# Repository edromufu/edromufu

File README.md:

### Hi there 👋

<!--
**edromufu/edromufu** is a ✨ _special_ ✨ repository because its `README.md` (this file) appears on your GitHub profile.

Here are some ideas to get you started:

- 🔭 I’m currently working on ...
- 🌱 I’m currently learning ...
- 👯 I’m looking to collaborate on ...
- 🤔 I’m looking for help with ...
- 💬 Ask me about ...
- 📫 How to reach me: ...
- 😄 Pronouns: ...
- ⚡ Fun fact: ...
-->

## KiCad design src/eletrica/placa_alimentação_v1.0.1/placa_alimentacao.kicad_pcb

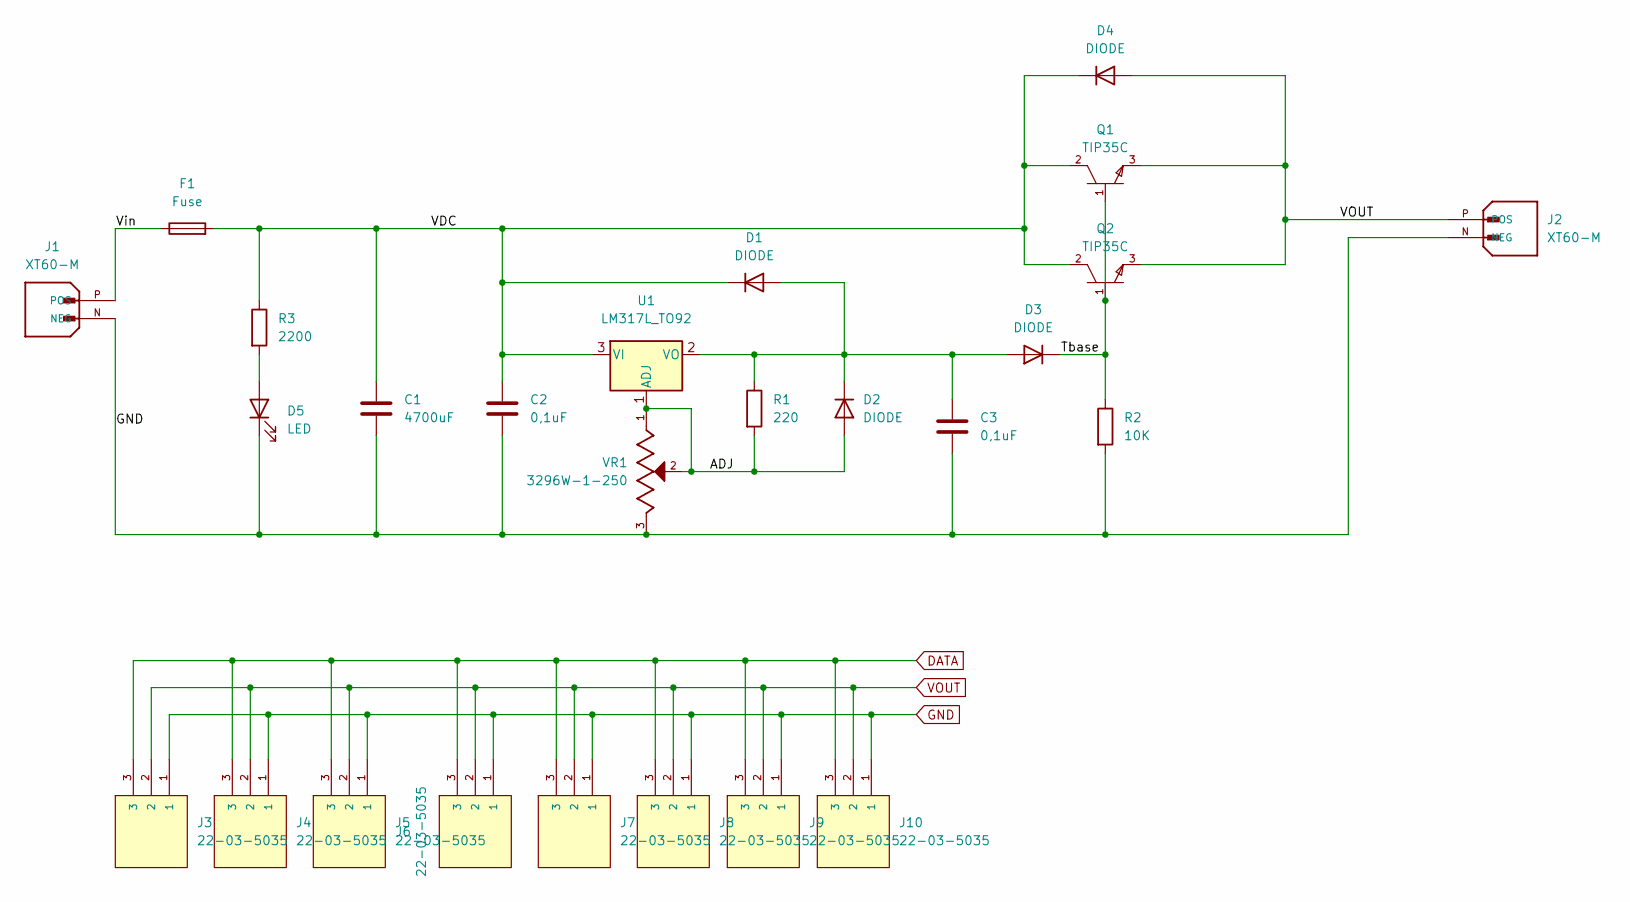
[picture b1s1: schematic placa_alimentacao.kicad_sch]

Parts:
C1: 4700uF; CP_Radial_D6.3mm_P2.50mm
C2, C3: 0,1uF; CP_Radial_D6.3mm_P2.50mm
D1, D2, D3, D4: DIODE; D_A-405_P12.70mm_Horizontal
D5: LED; LED_D3.0mm
F1: Fuse; Fuseholder_Cylinder-5x20mm_Schurter_0031_8201_Horizontal_Op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
J1, J2: XT60-M; AMASS_XT60-M; PARTREV V1.2
J3, J4, J5, J6, J7, J8, J9, J10: 22-03-5035; TTL_3pin; PARTREV B
Q1, Q2: TIP35C; TO-3PB-3_Vertical; voltage 100V; mouser part number 511-TIP35C; digikey description TRANS NPN 100V 25A TO-247
R1: 220; R_Axial_DIN0207_L6.3mm_D2.5mm_P7.62mm_Horizontal
R2: 10K; R_Axial_DIN0207_L6.3mm_D2.5mm_P7.62mm_Horizontal
R3: 2200; R_Axial_DIN0207_L6.3mm_D2.5mm_P7.62mm_Horizontal
U1: LM317L_TO92; TO-220-3_Vertical
VR1: 3296W-1-250; TRIM_3296W-1-250; PARTREV 05/16

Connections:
/ADJ: D2.1 (A), R1.2, U1.1 (ADJ), VR1.1, VR1.2
/Tbase: D3.2 (K), Q1.1 (BASE), Q2.1 (BASE), R2.1
/VDC: C1.1, C2.1, D1.2 (K), D4.2 (K), F1.2, Q1.2 (COLLECTOR), Q2.2 (COLLECTOR), R3.1, U1.3 (VI)
/Vin: F1.1, J1.P (POS)
DATA: J3.3, J4.3, J5.3, J6.3, J7.3, J8.3, J9.3, J10.3
GND: C1.2, C2.2, C3.2, D5.1 (K), J1.N (NEG), J2.N (NEG), J3.1, J4.1, J5.1, J6.1, J7.1, J8.1, J9.1, J10.1, R2.2, VR1.3
unnamed: C3.1, D1.1 (A), D2.2 (K), D3.1 (A), R1.1, U1.2 (VO)
unnamed: D5.2 (A), R3.2
VOUT: D4.1 (A), J2.P (POS), J3.2, J4.2, J5.2, J6.2, J7.2, J8.2, J9.2, J10.2, Q1.3 (EMITTER), Q2.3 (EMITTER)

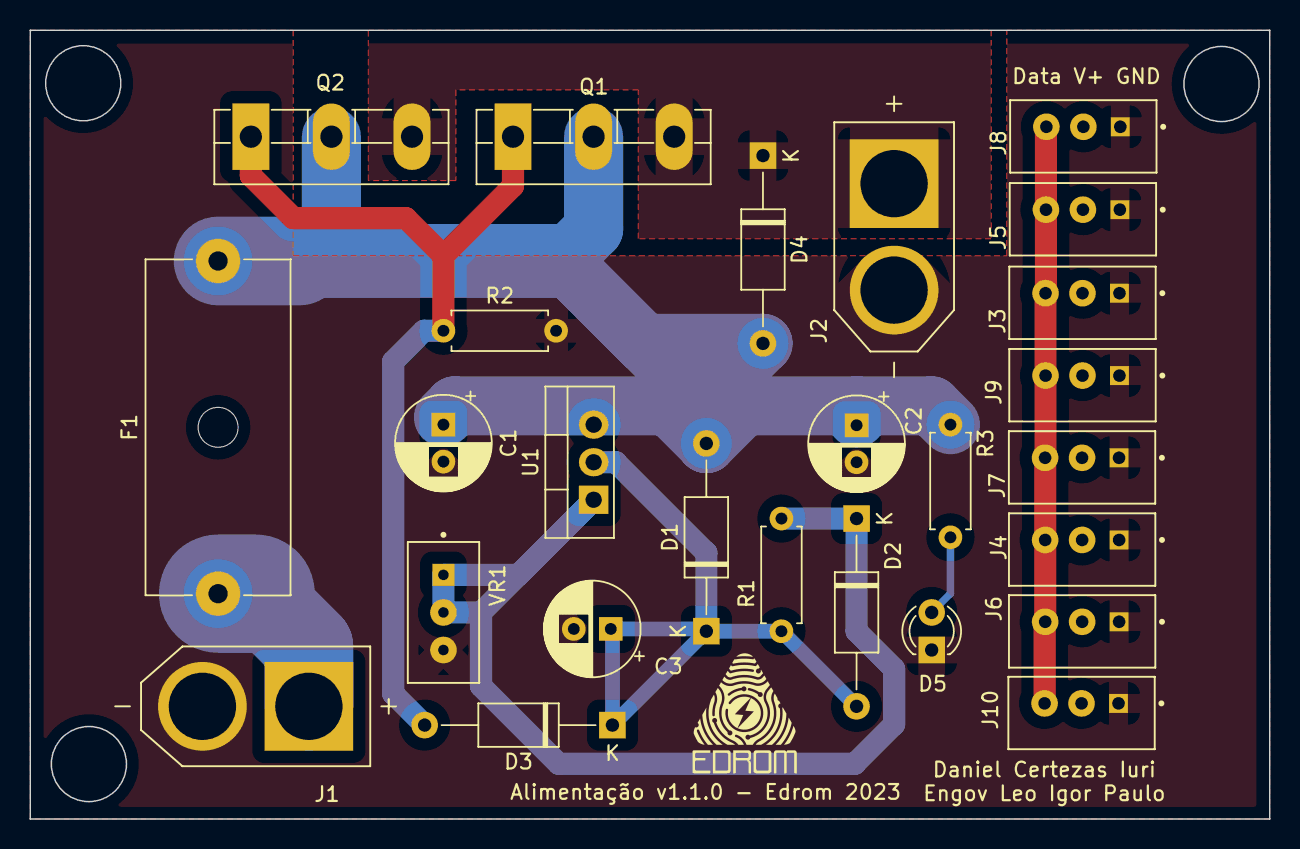
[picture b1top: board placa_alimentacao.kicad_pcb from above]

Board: 2 copper layers, 83.8 x 53.3 mm, 26 parts (0 on the bottom side), 9 nets.

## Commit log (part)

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2023-02-20 deploy: 3927a5f80aac86a664ac9377074125fa3db9a48a
2023-03-04 feat: updating SEO info
2023-03-09 Importação de .json no código de setup de robô, além de descrição da nova robô em .json.
2023-03-11 Alterações de QOL para o movimeto.
2023-03-11 Adição da cinemática direta funcional, com teste no setup_robot.py.
2023-03-15 Código da cinemática inversa.
2023-03-21 Adição dos motores invertidos, medidas da bioloid e alterações na mensagem de envio de posição aos motores.
2023-04-04 feat: adding placa da eletrica
2023-04-13 Page para VemPraUfu.
2023-04-27 Cinemática Inversa numérica funcional, remoção de pacotes iniciados antes da hora, alteração no .json da bioloid para mais complexo.
2023-04-28 Código da marcha funcional.
2023-05-04 Marcha funcional sem interpolação.
2023-05-05 Tentativa de interpolação.
2023-05-12 Solução burra de não conseguir chamar 2 marchas seguidas.
2023-05-12 deploy: 48f5c86a8db56971f9effe23fa8019512be7e65b
2023-05-12 deploy: de4b0d9f870d227b41426678e9c5c5853ad690d6
2023-05-12 deploy: 1f01412acf0f3dee689544b019c3a3a7313bde37
2023-05-12 deploy: cdb062678ca88378fecbfdf9b53d070c9acb654a
2023-05-12 deploy: 690ddbee62a3a7ab42929410748f4f81c1e6b5da
2023-05-12 deploy: 20d821d54e5ddaeca87752efcb6fc60e2abecab9
2023-05-12 deploy: 77052e3d364ca150665f6752ec5962a67bb86a9c
2023-05-13 deploy: a4d61b371b7a1144f42ccd0873185b7cab917576
2023-05-18 limitação dos joelhos para não quebrar
2023-05-26 Marcha sem interpolação funcional com joelho pro lado certo com problema de velocidade.
2023-06-01 Criação da classe padrão para juntas e início da classe padrão para robô.
2023-06-01 Fila no u2d2_comm
2023-07-03 Comunicação por grupos viável.
2023-07-03 Grupos funcionais e testado.
2023-07-10 Alterações no append não funcional da coree na comunicação com a u2d2.
2023-07-11 Removendo README da visão que gera conflito no merge com a dev.
2023-07-12 Interface no QtDesigner finalizada.
2023-07-12 Correção.
2023-07-17 Pacote da localizacao utilizando simulacao criado, parte da visao organizada com POO, commit para salvar alteracoes, mais testes serao feitos
2023-07-17 Funcionando para imagem, porem problemas na filtragem das interseccoes. Para testar no simulador, e necessario trocar o campo
2023-07-18 Teste para verificar tópico da estruturaaa
2023-07-18 Alterações restantes do QtDesigner.
2023-07-19 Botões já responsivos para o torque, posição atual sendo capturada e mostrada na tela.
2023-07-25 Pacote da localizacao real criado, com erro para matar o codigo. Intersecao filtrando corretamente, porem ajustes devem ser feitos. Ainda sem atualizacao das imagens quando utilizando ros (simulacao 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
2023-07-28 Resolvido bug de nao atualizar os frames, logica para evitar gargalos adicionada, mudanca na maneira de encontrar e verificar vizinhos, ainda nao foi possivel modificar o tamanho da imagem vinda da s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
2023-07-30 deploy: 2928f50e5e63d2a0b5530a4b819a7d1baaa1e23d
2023-07-30 deploy: 97fcbd00d635cccc3257c8d4f0158b8be7ad3756
2023-08-03 Commit do Igor
2023-08-04 Commit do Leo
2023-08-09 Pequena otimização na função de uncheck.
2023-08-10 Funcionalidade de salvar page implementada tanto para save quanto para saveAs.
2023-08-12 Cabeça funcional PARA A COMPETIÇÃO.
2023-08-12 Robô nova descrita em seu json, aparentemente a informação não esta sendo transmitida quando solicita-se publicação nos motores (u2d2 não pisca).
2023-08-18 Primeira tradução do código da simulação para o real
2023-08-22 BUG MX-106/MX-64
    Possível solução para não envio de posição para motores MX
2023-08-25 Codigo ligeiramente menos poluido
2023-08-29 Removendo movement antiga.
2023-08-30 Alterações do teste de marcha 29/08, software de pages funcional, conseguimos comandar posição pros motores, marcha não funcional.
2023-08-31 Visualizador pronto não integrado com a core.
2023-08-31 Visualizador funcional, pezinhos tortos na first_pose.
2023-09-02 Atualização do modelo da robô nova e de seu urdf.
2023-09-02 Separado corretamente e organizado o codigo, utilizando main temporaria para simulacao 2D
2023-09-05 deploy: 791abbdee91a0527ae1ee286bccd3fc24249245a
2023-09-05 deploy: 77e376e853058aa0c02f2170c94b71802796b567
2023-09-07 Page da natasha e atualização na core de QOL.
2023-09-10 IMU integrado com interpretações e testado, todas interpretações prontas sem teste.
2023-09-11 Implementações de QOL na leitura do código da u2d2, além de avisador de limites de motor. Não testado.
2023-09-11 Testado e funcional as implementações anteriores.
2023-09-12 Inicio da branch.
2023-09-16 Commitando para continuar de outro PC, nada funcional.
2023-09-17 Movimentação de procura e centralização da robô com NUC funcional, testar no NUC e implementar possível segundo código para PID.
2023-09-21 Tratamento de exceção no obtainMinMax.
2023-09-21 Calculador de poses do pé para caminhada pronto e não integrado (nem testado).
2023-09-24 Adicionando resize a visao para a melhora de FPS na jetson
2023-09-24 mudando os parametros de largura e altura da imagem da visao e mudando o nome do topico da visao
2023-09-25 First pose da aurea, teste do balanço funcional e interpolação para pose inicial.
2023-09-26 First pose da Natasha
2023-09-30 Removendo interpolação no geral.
2023-09-30 Pages da goleira funcional finalizando as defesas de costas,não há pages de se levantar.
2023-10-03 Inicio do desenvolvimento da caminhada dinamica para aurea completamente montada e page de levantar de frente 95% pronta.
2023-10-04 Revisão da caminhada - tunagem de parametros
2023-10-06 Criação de código falso da u2d2 para eliminar necessidade de plugar a robô em testes básicos e/ou de visualização, implementação das correções aplicadas no COM do modelo (.json) da robô na visualizaç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
2023-10-06 Separando os arquivos de geração de padrões para facilitar implementações.
2023-10-08 Desenvolvimento dia 0 - Warm up.
2023-10-09 behaviour, talvez ta pronto, sem testes
2023-10-09 visao
2023-10-09 bota essa porra
2023-10-09 behaviour ainda nao testado
2023-10-09 page levantar de costas
2023-10-09 behaviour goleira pra testes
2023-10-09 separacao dos codigos da aurea
2023-10-09 Page modificada de levantar de costas ainda não funcional.
2023-10-10 BEhaviour da goleira: Chamando page de defesa de acordo com ball close e posição da cabeça.
2023-12-18 Testando o versionamento para ambiente em ROS2
2023-12-19 Adição de arquivo teste para yolov8
2023-12-22 Início das modificações dos códigos para YOLOv8
2024-01-23 Adição de comentários dos possíveis erros do código da caminhada
2024-02-03 Termino ros2 codigo principal, adição do vision_msgs em ros2 e organização dos pacotes
2024-03-02 Organização dos pacotes ros
2024-03-04 Correção dos nomes das msgs e srvs
2024-03-15 resolve ae
2024-04-05 Agora tá certo
2024-04-11 Adição do pacote movement_pages em ros2
2024-04-13 criacao do codigo do esp master, com o espnow e microros-envio
2024-05-02 Inicio do movement core e algumas atualizações
2024-05-02 Ultimas alterações Ros2 de movement core e u2d2 comm
2024-05-03 deploy: 8e37eca30fbd863d5a9b1add2666fdafd078992a
2024-05-03 deploy: df0c3623d7106ddbe779e2379d6df7809b16fd7a
2024-05-07 adicao do json da robo Nova
2024-05-10 Criação do diretório ros2_change e adição do pacote bhv_independent_simulator já em ros2
2024-05-14 commit do urdf da robô nova - corrigido
2024-05-14 bixo
2024-05-14 deploy: 9ecaed26f4d94e8f1ec4455449b08666a6d2ff9b
2024-05-15 Inicio documentação software de pages
2024-05-15 deploy: 347dbef622f833e3426834465e34263cb3b00144
2024-05-15 inicio documentação pages
2024-05-15 Correção de erro de envio do movement_core para o git
2024-05-20 add rviz example with the roblox urdf
2024-05-21 deploy: 071a21bc94def8edc6dc8fa721b2088f28050971
2024-05-21 fixing the package urdf_example
2024-05-21 deploy: 0e827dbdc95c0db04296e857ac38aded1c67898d
2024-05-22 teste
2024-05-24 add micro ros packages and esp code
2024-05-24 Alterações no core e launch // adição do .json e .urdf nos diretórios corretos
2024-05-29 Update connecting_and_showing.md
    Apagar show result frame
2024-06-07 states_routine e modularized_bhv_msgs para ROS2
2024-06-07 Update criando_txts_dataset.md
    Nova organização do dataseet
    Não consegui adicionar os printes dos exemplos dos passos a serem seguidos
    https://docs.google.com/document/d/1RCSKG2EgAhYPeM73om0e6j2ff42ELxX2zQ4pJqjIhng/edit?usp=sharing
    esse link da acesso ao docs com os printes que estão ausentes
2024-06-07 Update connecting_and_showing.md
    Troca para nova estrutura de códigos, retirada do show result frame e atualização das funções para ROS2
2024-06-07 deploy: 09d5faeb3f88a29ac4e7282ea905cc4f7c7fe130
2024-06-07 sensor_observer ros2
2024-06-08 Pequenas alterações documentação e adição de arquivos importantes
2024-06-08 Teste camera no nuc com mudança no tamanho da imagem, 30 FPS na inferencia
2024-06-19 Adição dos últimos arquivos da documentação com correções
2024-06-21 read write joint needs real test
2024-06-22 pid de uma perna só
2024-06-28 testing actuators
2024-07-05 Atualização da documentação da visão
2024-07-08 Build dos pacotes states_routine e modularized_bhv_msgs
2024-07-08 buildando ros 2 pacotes
2024-07-16 Revertendo arquivos da documentação para não causar conflito de merge em dev-ROS2
2024-08-13 Adicionando a pasta de simulação da robox
2024-08-16 Adição do código da IK Analitica
2024-08-16 Pequenas alterações no codigo da localização
2024-08-17 game controller começo
2024-08-18 Falta configurar o MUX no Pot Pub
2024-08-29 testes gamecontroller, funções basicas implementadas
2024-09-05 Codigo do Subscriber com Publisher de Feedback
2024-09-14 micro_ros_library
2024-09-21 update sim
2024-09-21 Alterações feitas na sede nos códigos de leitura e escrita baseados nos referenciais novos adotados
2024-09-28 Correção do código da cinemática e inicio das mudanças relacionadas a nova camera
2024-10-09 atualizações para comunicação com o gamecontrole em statemachine
2024-10-09 Add as novas msgs, add subscriber nos codigos dos atuadores
2024-10-10 comentaŕios para tarefas do behaviour
2024-10-10 Pot to Degrees
2024-10-12 MicroROS publisher e subscriber funcionando
2024-10-18 Json teste da robo nova atualizado
2024-10-18 Atualização das mensagens da visão
2024-10-23 atualizações bhv
2024-11-01 Behaviour da atacante (Precisa de alterações)
2024-11-01 Versão Inicial Software de Pages Tahara
2024-11-02 fim software de pages, alteração no publisher na core
2024-11-02 micro ros
2024-11-05 adicao do gameControllerMsg
2024-11-05 Criacao do pacote game_controller
2024-11-07 Fim da comunicação entre esp's. O esp atuador está recebendo o vetor de erro direto. Comunicação entre o software de pages e o publisher de potenciômetro
2024-11-10 Parametros de queda
2024-11-11 Atualizar o imu.ino
2024-11-11 Correcao do codigo imu
2024-11-11 Código localização runVision quase completo
2024-11-11 Configuracao do Cmake e package.xml
2024-11-11 mudança nos codigos dos esps
2024-11-11 Feedback poses
2024-11-12 ta com atraso na lista
2024-11-12 criação branch tahara
2024-11-12 Debug do game controller, alteração na build das mensagens Co-authored-by: Bruno Augusto <sierbruno001@gmail.com> Co-authored-by: Gustavo Brazilino <gustavobrazilino@gmail.com> Co-authored-by: Leonar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
2024-11-13 terça feira, tahara se mecheu pela primeira vez, faltou testar sentido dos potenciometros
2024-11-13 alterações na visao
2024-11-13 Debug visão, procura bola e pages. (Bruno)
2024-11-13 launch goleira
2024-11-13 fix atuadores.ino
2024-11-14 fix: modificaçao behaviour aurea
2024-11-14 feat: mudanças na first pose, walk left e walk right da aurea 2024
2024-11-15 behaviour
2024-11-15 fix: goalkeeper e o u2d2 comm
2024-11-15 atualização das portas do esp depois do consertar o curto
2024-11-16 Chute angulado com braço apoiado
2024-11-16 Pré Ita, Testes na tahara, controle de juntas individuais funcionando
2024-11-16 Page dança padrao
2024-12-06 fix(core, core_head, dynamixel_sdk_comm) - Fixing the error found when .launch was executed
2024-12-09 Codigo de teste dos pinos PWM
2024-12-09 Alteraçao no arquivo teste
2024-12-10 Pinos do driver
2024-12-11 Alterações Tahara_Launch e ErrorPackage
2024-12-12 Só falta ajustar e testar na Alice
2024-12-16 Perna Esquerda funcionando
2025-06-18 Inicio da atualização da simulação para ROS2(launch, package, setup), incluindo mudanças na estrutura dos arquivos
2025-06-25 commit para teste de ambiente
